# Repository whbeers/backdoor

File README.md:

# Backdoor Distortion Effect

This is my take on the ProCo "Rat" distortion effect, designed in [KiCAD](https://www.kicad.org/).  The design is based on widely available schematics and pretty true to the original Rat, with only a couple part value swaps that came from experimentation on a breadboard with my daughter. (She was involved in every stage of the development of this effect, and learned a ton!)

The board is built on the ["Noise Floor"](https://github.com/whbeers/noise_floor) pedal platform, which provides basic power protection, audio IO, and a footswitch with LED indicator.

[Schematic PDF](schematics/backdoor-latest.pdf)

## Credit
The initial breadboarding utilized the schematic included in the ProCo Rat Analysis at [Electrosmash](https://www.electrosmash.com/proco-rat).

The Rat has a really interesting history - to learn more about it I recommend the [JHS Show episode on the subject](https://www.youtube.com/watch?v=QfwpClT_26E), and for more circuit analysis Brian Wampler has published [several](https://www.youtube.com/watch?v=zBGKdnlh4Ws) [youtube](https://www.youtube.com/watch?v=IAt-hgqrocI) [videos](https://www.youtube.com/watch?v=U2ZOTbfAcNs) going over the circuit and potential tweaks, including their own (tweaked) clone.

Thanks as always to the folks on the [freestompboxes.org](https://www.freestompboxes.org/) forum for feedback and suggestions.

Potentiometer 3D model courtesy [Vasily Kashirin](https://grabcad.com/vasily.kashirin-1).

*I am not affiliated with any of the brands, sites, or products named in this overview.*

## Versioning

My pcb designs utilize the following versioning scheme (I'll add to this as I produce more revisions):
 - v0.0XX: A candidate design that has not yet been produced and tested.
 - v0.XX: A design that has been produced, tested, and any initial errors addressed.

## Name
*The name "Backdoor" is a reflection of the nature of the effect (a RAT) and security nerdery.*

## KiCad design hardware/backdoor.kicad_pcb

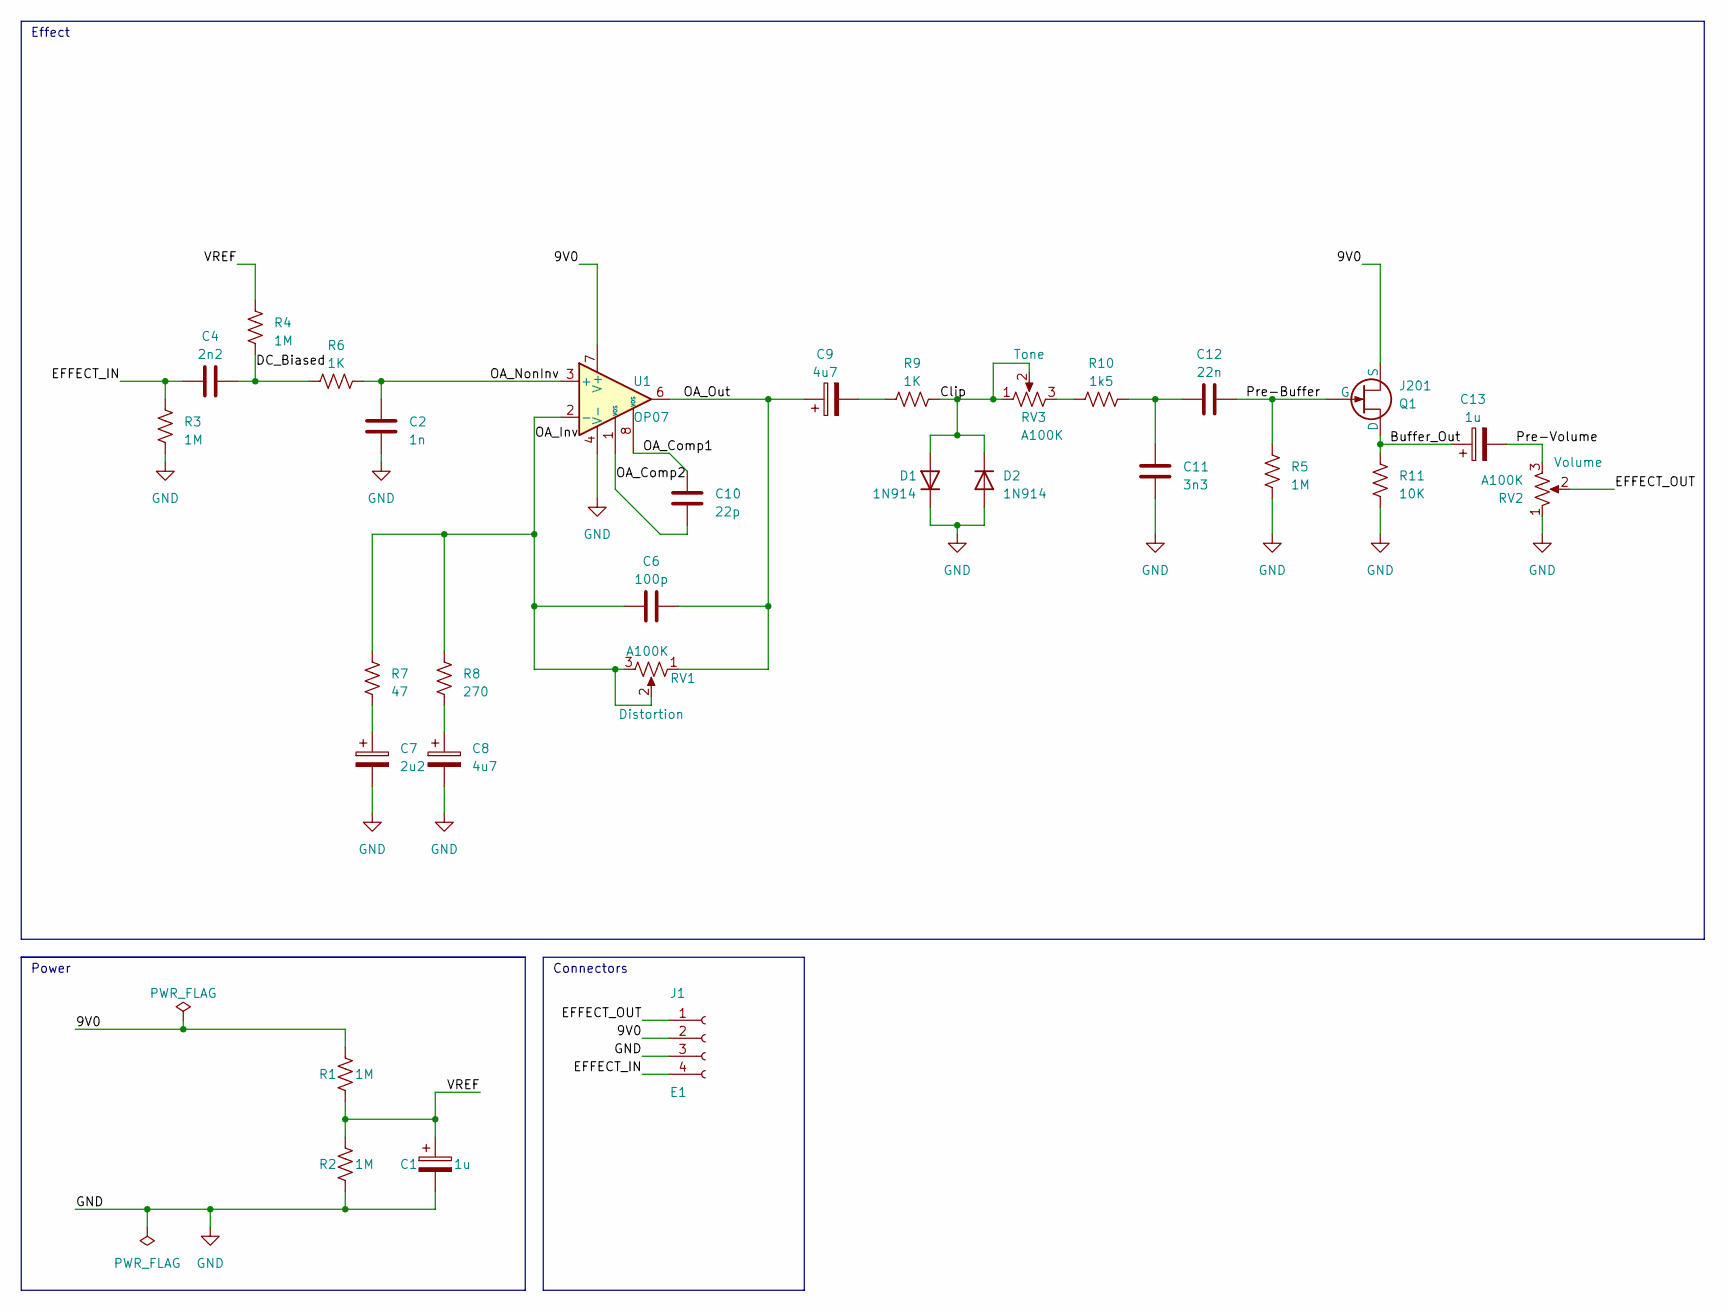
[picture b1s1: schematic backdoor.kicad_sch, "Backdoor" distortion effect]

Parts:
C1, C13: 1u; CP_Radial_D5.0mm_P2.50mm
C2: 1n; C_Rect_L7.2mm_W2.5mm_P5.00mm_FKS2_FKP2_MKS2_MKP2
C4: 2n2; C_Rect_L7.2mm_W2.5mm_P5.00mm_FKS2_FKP2_MKS2_MKP2
C6: 100p; C_Rect_L7.2mm_W2.5mm_P5.00mm_FKS2_FKP2_MKS2_MKP2
C7: 2u2; CP_Radial_D5.0mm_P2.50mm
C8, C9: 4u7; CP_Radial_D5.0mm_P2.50mm
C10: 22p; C_Rect_L7.2mm_W2.5mm_P5.00mm_FKS2_FKP2_MKS2_MKP2
C11: 3n3; C_Rect_L7.2mm_W2.5mm_P5.00mm_FKS2_FKP2_MKS2_MKP2
C12: 22n; C_Rect_L7.2mm_W2.5mm_P5.00mm_FKS2_FKP2_MKS2_MKP2
D1, D2: 1N914; D_DO-34_SOD68_P7.62mm_Horizontal
J1: E1; Molex_PicoBlade_53047-0410_1x04_P1.25mm_Vertical_with_3D_Mo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
Q1: J201; TO-92_Inline
R1, R2, R3, R4, R5: 1M; R_Axial_DIN0207_L6.3mm_D2.5mm_P7.62mm_Horizontal
R6, R9: 1K; R_Axial_DIN0207_L6.3mm_D2.5mm_P7.62mm_Horizontal
R7: 47; R_Axial_DIN0207_L6.3mm_D2.5mm_P7.62mm_Horizontal
R8: 270; R_Axial_DIN0207_L6.3mm_D2.5mm_P7.62mm_Horizontal
R10: 1k5; R_Axial_DIN0207_L6.3mm_D2.5mm_P7.62mm_Horizontal
R11: 10K; R_Axial_DIN0207_L6.3mm_D2.5mm_P7.62mm_Horizontal
RV1, RV2, RV3: A100K; Potentiometer_Single_3_Horizontal
U1: OP07; DIP-8_W7.62mm

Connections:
/9V0: J1.2, Q1.1 (S), R1.2, U1.7 (V+)
/Buffer_Out: C13.1, Q1.2 (D), R11.1
/Clip: D1.2 (A), D2.1 (K), R9.2, RV3.1, RV3.2
/DC_Biased: C4.2, R4.2, R6.1
/EFFECT_IN: C4.1, J1.4, R3.1
/EFFECT_OUT: J1.1, RV2.2
/OA_Comp1: C10.2, U1.8 (VOS)
/OA_Comp2: C10.1, U1.1 (VOS)
/OA_Inv: C6.1, R7.1, R8.1, RV1.2, RV1.3, U1.2 (-)
/OA_NonInv: C2.1, R6.2, U1.3 (+)
/OA_Out: C6.2, C9.1, RV1.1, U1.6
/Pre-Buffer: C12.2, Q1.3 (G), R5.1
/Pre-Volume: C13.2, RV2.3
/VREF: C1.1, R1.1, R2.2, R4.1
GND: C1.2, C2.2, C7.2, C8.2, C11.2, D1.1 (K), D2.2 (A), J1.3, R2.1, R3.2, R5.2, R11.2, RV2.1, U1.4 (V-)
unnamed: C7.1, R7.2
unnamed: C8.1, R8.2
unnamed: C9.2, R9.1
unnamed: C11.1, C12.1, R10.2
unnamed: R10.1, RV3.3

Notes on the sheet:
Connectors
Power
Effect

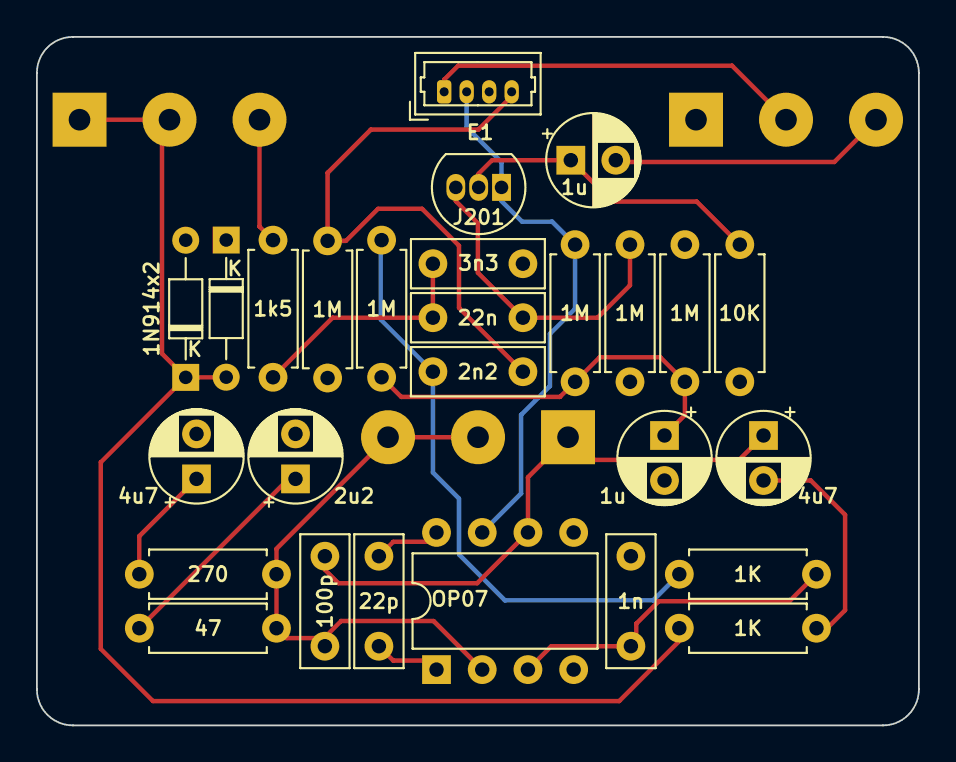
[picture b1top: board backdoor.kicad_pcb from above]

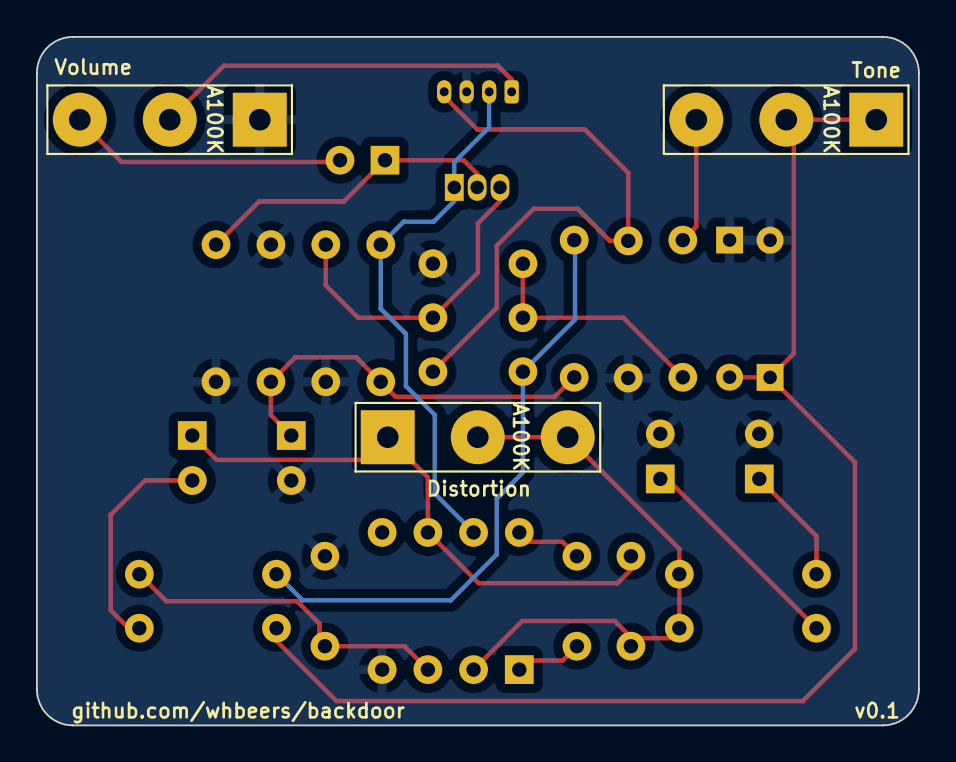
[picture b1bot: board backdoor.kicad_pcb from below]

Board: 2 copper layers, 49.0 x 38.2 mm, 30 parts (3 on the bottom side), 20 nets.

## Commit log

2023-03-10 initial (empty) project for backdoor RAT effect
2023-03-10 initial schematic for Backdoor
2023-03-10 Readme updates
2023-03-10 script updates
2023-03-17 add disclaimer
2023-03-19 Add values after experimenting on the breadboard
2023-03-26 initial layout and renders, bump rev to v0.02
2023-03-27 make readme consistent with others
2023-03-29 Routed v0.02, ready for fabrication
2023-03-29 fix renders
2023-04-16 Fix issue identified in v0.02 hardware
    - update schematic to use correct pin for jfet output buffer
2023-04-17 update schematic
